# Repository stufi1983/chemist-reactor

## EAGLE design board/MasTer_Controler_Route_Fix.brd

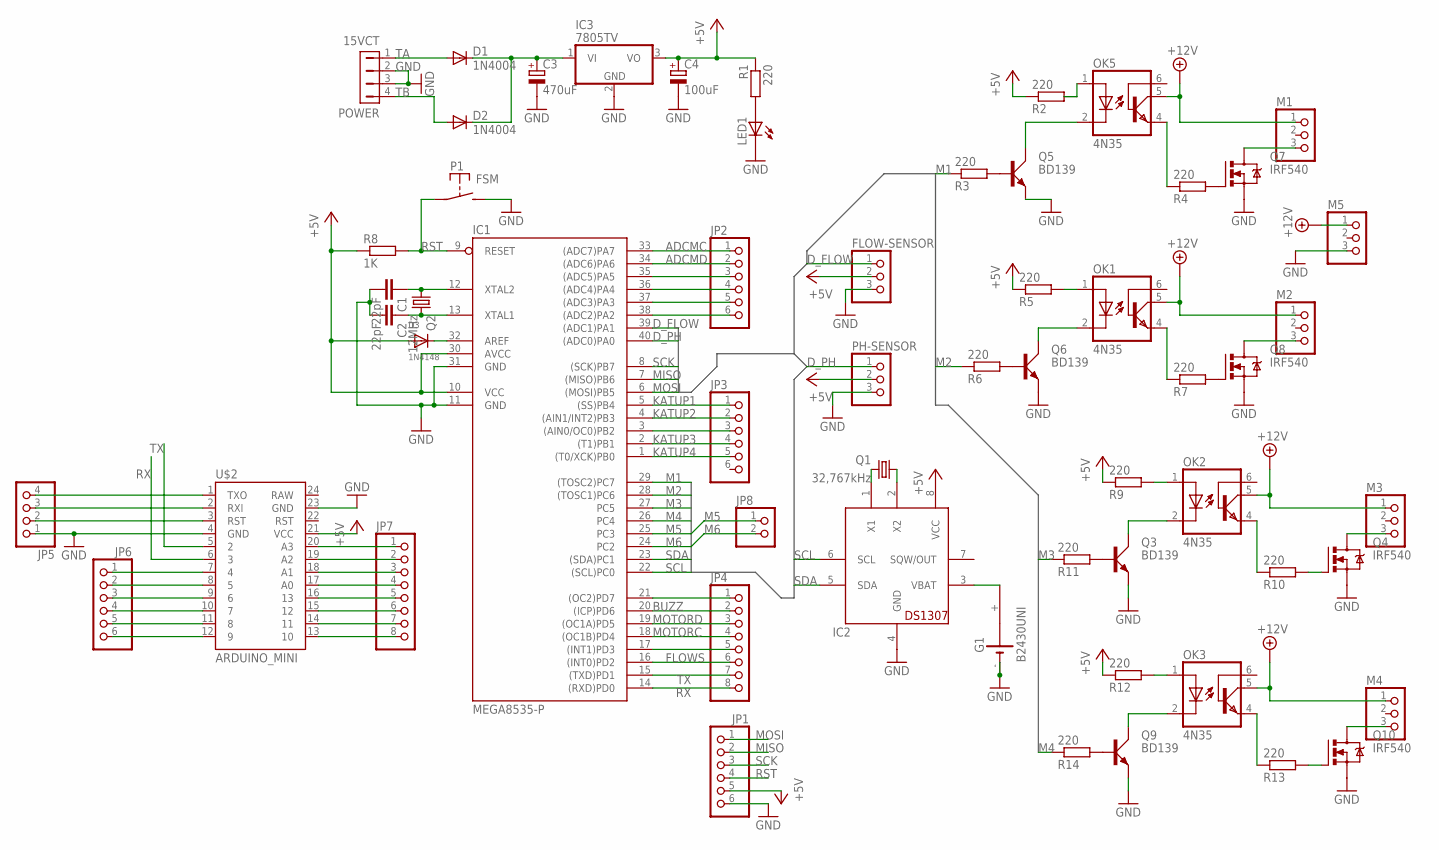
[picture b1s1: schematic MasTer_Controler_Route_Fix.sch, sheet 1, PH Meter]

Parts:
15VCT: POWER; MTA-100-4V
C1, C2: 22pF; C2.5-4
C3: 470uF; E5-6
C4: 100uF; E5-6
D1, D2: 1N4004; DO41-10
D3: 1N4148; DO-1N4148
FLOW-SENSOR: PINHD-1X3; 1X03
G1: B2430UNI
IC1: MEGA8535-P; DIL40
IC2: DS1307; DIL08
IC3: 7805TV; TO220V
JP1, JP2, JP3: PINHD-1X6; 1X06
JP4, JP7: PINHD-1X8CLEANBIG; 1X08-CLEANBIG
JP5: PINHD-1X4; 1X04
JP6: PINHD-1X6CB; 1X06-CLEANBIG
JP8: PINHD-1X2; 1X02
LED1: LED5MM
M1, M2, M3, M4, M5: PINHD-1X3; 1X03
OK1, OK2, OK3: 4N35; DIL06; MPN 4N35
OK5: 4N35; DIL06
P1: FSM
PH-SENSOR: PINHD-1X3; 1X03
Q1: 32,767kHz; TC26H
Q2: 12MHz; HC49U70
Q3, Q5, Q6, Q9: BD139; TO126AV
Q4, Q7, Q8, Q10: IRF540; TO220BV
R1, R2, R3, R4, R5, R6, R7, R9, R10, R11, R12, R13, R14: 220; 0207/10
R8: 1K; 0207/10
U$2: ARDUINO_MINI

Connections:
+5V: C4.+, D3.A, FLOW-SENSOR.2, IC1.10 (VCC), IC1.30 (AVCC), IC2.8 (VCC), IC3.3 (VO), JP1.5, PH-SENSOR.2, R1.1, R2.1, R5.1, R8.1, R9.1, R12.1, U$2.21 (VCC)
+12V: M1.1, M2.1, M3.1, M4.1, M5.1, OK1.5 (COL), OK2.5 (COL), OK3.5 (COL), OK5.5 (COL)
ADCMC: IC1.33 ((ADC7)PA7), JP2.1
ADCMD: IC1.34 ((ADC6)PA6), JP2.2
BUZZ: IC1.20 ((ICP)PD6), JP4.2
D_FLOW: FLOW-SENSOR.1, IC1.39 ((ADC1)PA1)
D_PH: IC1.40 ((ADC0)PA0), PH-SENSOR.1
FLOWS: IC1.16 ((INT0)PD2), JP4.6
GND: 15VCT.2, 15VCT.3, C1.2, C2.2, C3.-, C4.-, FLOW-SENSOR.3, G1.-, G1.-@1 (-), IC1.11 (GND), IC1.31 (GND), IC2.4 (GND), IC3.2 (GND), JP1.6, JP5.1, LED1.K (C), M5.3, P1.P$2 (S), PH-SENSOR.3, Q3.E, Q4.S, Q5.E, Q6.E, Q7.S, Q8.S, Q9.E, Q10.S, U$2.4 (GND), U$2.23 (GND)
KATUP1: IC1.5 ((SS)PB4), JP3.1
KATUP2: IC1.4 ((AIN1/INT2)PB3), JP3.2
KATUP3: IC1.2 ((T1)PB1), JP3.4
KATUP4: IC1.1 ((T0/XCK)PB0), JP3.5
M1: IC1.29 ((TOSC2)PC7), R3.1
M2: IC1.28 ((TOSC1)PC6), R6.1
M3: IC1.27 (PC5), R11.1
M4: IC1.26 (PC4), R14.1
M5: IC1.25 (PC3), JP8.1
M6: IC1.24 (PC2), JP8.2
MISO: IC1.7 ((MISO)PB6), JP1.2
MOSI: IC1.6 ((MOSI)PB5), JP1.1
MOTORC: IC1.18 ((OC1B)PD4), JP4.4
MOTORD: IC1.19 ((OC1A)PD5), JP4.3
unnamed: IC2.1 (X1), Q1.2
unnamed: IC2.2 (X2), Q1.1
unnamed: C1.1, IC1.12 (XTAL2), Q2.1
unnamed: C2.1, IC1.13 (XTAL1), Q2.2
unnamed: G1.+, IC2.3 (VBAT)
unnamed: LED1.A, R1.2
unnamed: C3.+, D1.C, D2.C, IC3.1 (VI)
unnamed: OK5.1 (A), R2.2
unnamed: OK5.2 (C), Q5.C
unnamed: Q5.B, R3.2
unnamed: Q7.G, R4.2
unnamed: OK5.4 (EMI), R4.1
unnamed: Q8.G, R7.2
unnamed: OK1.1 (A), R5.2
unnamed: OK1.2 (C), Q6.C
unnamed: Q6.B, R6.2
unnamed: M1.3, Q7.D
unnamed: OK1.4 (EMI), R7.1
unnamed: M2.3, Q8.D
unnamed: IC1.35 ((ADC5)PA5), JP2.3
unnamed: IC1.36 ((ADC4)PA4), JP2.4
unnamed: IC1.37 ((ADC3)PA3), JP2.5
unnamed: IC1.38 ((ADC2)PA2), JP2.6
unnamed: IC1.3 ((AIN0/OC0)PB2), JP3.3
unnamed: IC1.21 ((OC2)PD7), JP4.1
unnamed: IC1.17 ((INT1)PD3), JP4.5
unnamed: JP5.4, U$2.1 (TXO)
unnamed: OK2.1 (A), R9.2
unnamed: OK2.2 (C), Q3.C
unnamed: D3.C, IC1.32 (AREF)
unnamed: OK2.4 (EMI), R10.1
unnamed: M3.3, Q4.D
unnamed: Q3.B, R11.2
unnamed: Q4.G, R10.2
unnamed: JP5.3, U$2.2 (RXI)
unnamed: OK3.1 (A), R12.2
unnamed: OK3.2 (C), Q9.C
unnamed: OK3.4 (EMI), R13.1
unnamed: M4.3, Q10.D
unnamed: Q9.B, R14.2
unnamed: Q10.G, R13.2
unnamed: JP5.2, U$2.3 (RST)
unnamed: JP6.1, U$2.7 (4)
unnamed: JP6.2, U$2.8 (5)
unnamed: JP6.3, U$2.9 (6)
unnamed: JP6.4, U$2.10 (7)
unnamed: JP6.5, U$2.11 (8)
unnamed: JP6.6, U$2.12 (9)
unnamed: JP7.1, U$2.20 (A3)
unnamed: JP7.2, U$2.19 (A2)
unnamed: JP7.3, U$2.18 (A1)
unnamed: JP7.4, U$2.17 (A0)
unnamed: JP7.5, U$2.16 (13)
unnamed: JP7.6, U$2.15 (12)
unnamed: JP7.7, U$2.14 (11)
unnamed: JP7.8, U$2.13 (10)
RST: IC1.9 (RESET), JP1.4, P1.P$1, R8.2
RX: IC1.14 ((RXD)PD0), JP4.8, U$2.6 (3)
SCK: IC1.8 ((SCK)PB7), JP1.3
SCL: IC1.22 ((SCL)PC0), IC2.6 (SCL)
SDA: IC1.23 ((SDA)PC1), IC2.5 (SDA)
TA: 15VCT.1, D1.A
TB: 15VCT.4, D2.A
TX: IC1.15 ((TXD)PD1), JP4.7, U$2.5 (2)

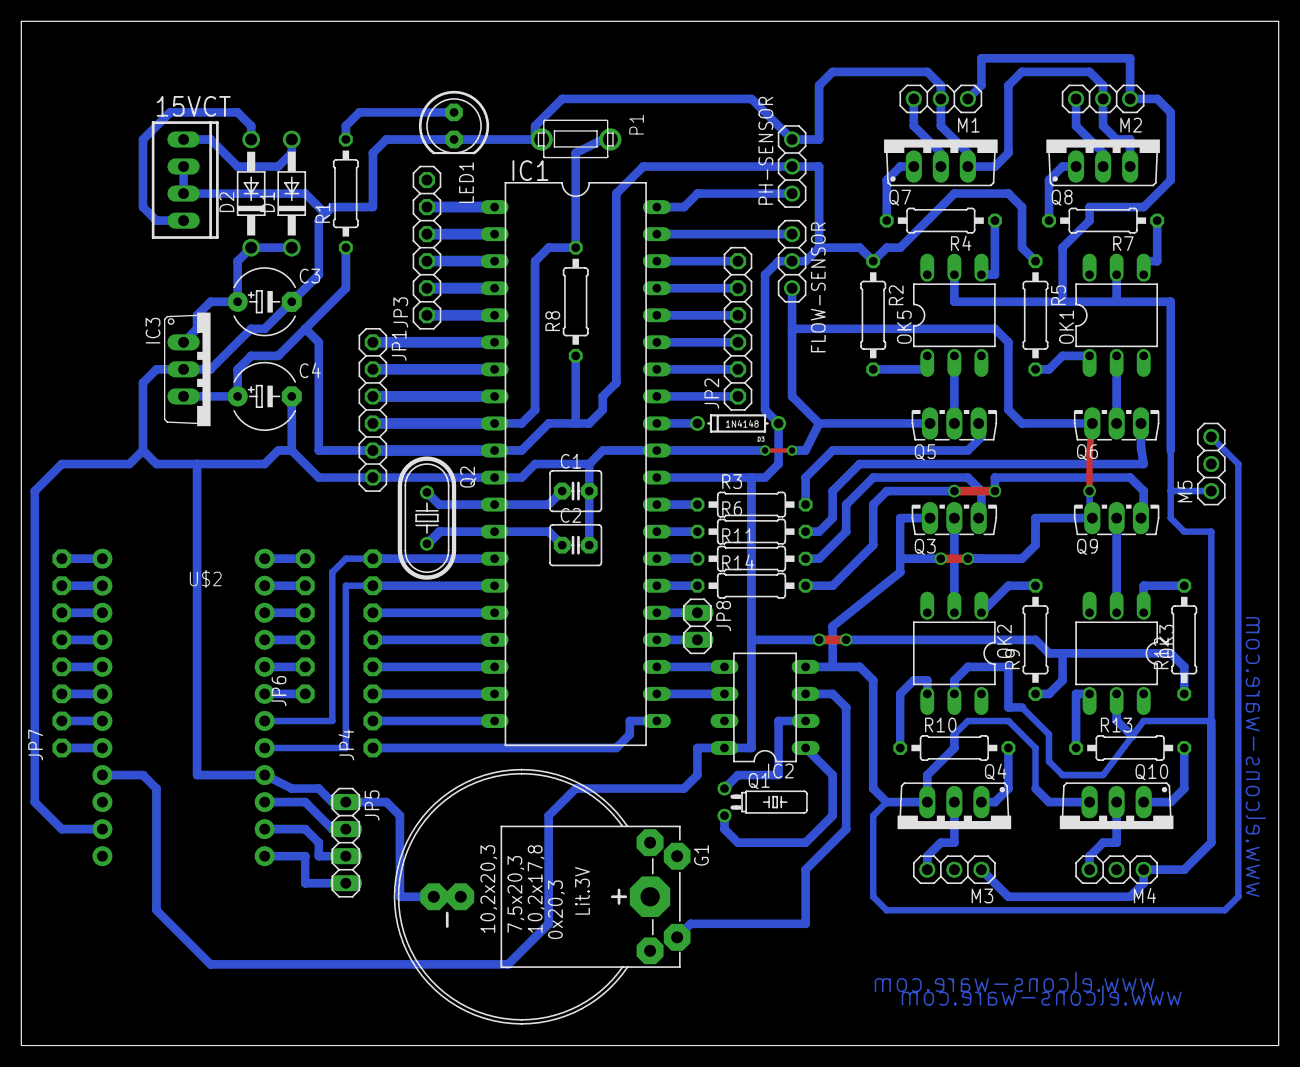
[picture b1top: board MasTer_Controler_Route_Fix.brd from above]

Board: 2 copper layers, 118.1 x 96.2 mm, 58 parts (0 on the bottom side), 87 nets.

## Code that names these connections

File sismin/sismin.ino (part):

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const byte Output[rows] = {23, 22, 21, 20}; //array of pins used as output for rows of keypad
const byte Input[columns] = {29, 28, 27, 26}; //array of pins used as input for columnss of keypad

#define FLOWINTERRUPT   //koneksi flow sensor,pilih: FLOWINTERRUPT di pin INT0/16 atau FLOWDIGITAL di pin PA1/39

//NB: urutan pin header untukflow sensor di PCB tidak pas dengan sensor
#define NOTCEKFLOW         //test Flow Sensor, pilih: CEKFLOW untuk test atau NOTCEKFLOW untuk normal
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
#define BUZZER   14

#define  KATUP1  4//pb4
#define  KATUP2  3//pb3
#define  KATUP3  1//pb1
#define  KATUP4  0//pb0

//Timer masih dummy
#define TIMERBAKA  30
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#define TIMERBAKE  12  //3600*4 
#define TIMERBAKF  12  //3600 

#define MOTORA    23 //PC7  --->HARUSNYA DI OUTPUT TIMER 
#define MOTORB    22 //PC6
#define MOTORC    12 //PD4  --->HARUSNYA DI OUTPUT TIMER
#define POTMOTORC A7
#define MOTORD    13 //PD5  --->HARUSNYA DI OUTPUT TIMER
#define POTMOTORD A6

#define PERISA    19 //PC3
#define PERISB    18 //PC2

#define MAXDIGIT  6

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byte byteNum = 0;
byte int2bytebuf[MAXDIGIT];

#define FLOWSENSOR  A1 //PA1 -->HARUSNYA DI PIN INTERRUPT
unsigned long debit = 1;
unsigned int RisingEdgeCounter = 0;
volatile int RisingEdgeCounterInt;
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}

void resetPin() {
  const byte OutputPin[] = {BUZZER, KATUP1, KATUP2, KATUP3, KATUP4, MOTORA, MOTORB, MOTORC, MOTORD, PERISA, PERISB, FLOWSENSOR};
  for (byte i = 0; i < sizeof(OutputPin); i++) {
    pinMode(OutputPin[i], OUTPUT); digitalWrite(OutputPin[i], LOW);
  }
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    pinMode(BUZZER, OUTPUT);
    digitalWrite(BUZZER, LOW);

    pinMode(KATUP1, OUTPUT);
    digitalWrite(KATUP1, LOW);
    pinMode(KATUP2, OUTPUT);
    digitalWrite(KATUP2, LOW);
    pinMode(KATUP3, OUTPUT);
    digitalWrite(KATUP3, LOW);
    pinMode(KATUP4, OUTPUT);
    digitalWrite(KATUP4, LOW);

    pinMode(MOTORA, OUTPUT);
    digitalWrite(MOTORA, LOW);
    pinMode(MOTORB, OUTPUT);
    digitalWrite(MOTORB, LOW);
    pinMode(MOTORC, OUTPUT);
    digitalWrite(MOTORC, LOW);
    pinMode(MOTORD, OUTPUT);
    digitalWrite(MOTORD, LOW);

    pinMode(PERISA, OUTPUT);
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      RisingEdgeCounter = 0;
      startMillis = millis();

#ifdef FLOWINTERRUPT //pakai interrupt 0 / PD2 / D10 /pin ic 16
      RisingEdgeCounterInt = 0;
      attachInterrupt(0, flowInterrupt, RISING); // Setup Interrupt
      //sei();
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
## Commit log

2015-10-05 First commit, initial project
2015-10-05 Added: Main Board schematic and layout (EagleCAD)
2015-10-05 Added: 3D design board
2015-10-06 Testing minimum system
2015-10-07 Added promini sketch
2015-10-08 Fix: Serial to LCD in promini
    Add: Serial test
2015-10-09 Fix: sketchcr A0 to pin number (30)
    Fix: promini to ignore println (0D 0A)
    Fix: promini only display filled buffer (bytes) to LCD
2015-10-10 Add: promini: Pin configuration for LCD
2015-10-10 Add:
    promini:
    Display Texts 1 to 14
    Value on text in display #2
    Parsing serial D for Display Text followed by for values
    sismin:
    Send Display Text #1 for 5 seconds
2015-10-10 Add: LCD Serial Doc
2015-10-11 Added:
    sismin sensors measurement
    promini realign char on LCD
    promini re-display entry value when accepted
    Bug:
    sismin ph sensor
    Next:
2015-10-11 Add:
    promini baca sensor LCD text D0
    sismin:
    definition to cek individual sensor
    buzzer pin 14
    flow sensor pin A1 ---> should be moved to INT0
    INT0 ISR for flow sensor
2015-10-12 Board diedit
2015-10-12 Added potentio to set motor speed
2015-10-13 cek keypad
2015-10-16 Add: Keypad function
    Bug: Flash full... need to be optimized
2015-10-16 Add: Keypad upper limit value
2015-10-17 promini: add Proses penetesan edit cursor ph dan entry
    sismin: rombak variabel perbaiki entry keypad fungsikan katup fungsikan peristaltik

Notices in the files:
parts and their libraries:
con-hdrs40: Copyright (C) 2004, Bob Starr (bobstarr@mindspring.com)
SparkFun-Boards: Licensing: Creative Commons ShareAlike 4.0 International - https://creativecommons.org/licenses/by-sa/4.0
